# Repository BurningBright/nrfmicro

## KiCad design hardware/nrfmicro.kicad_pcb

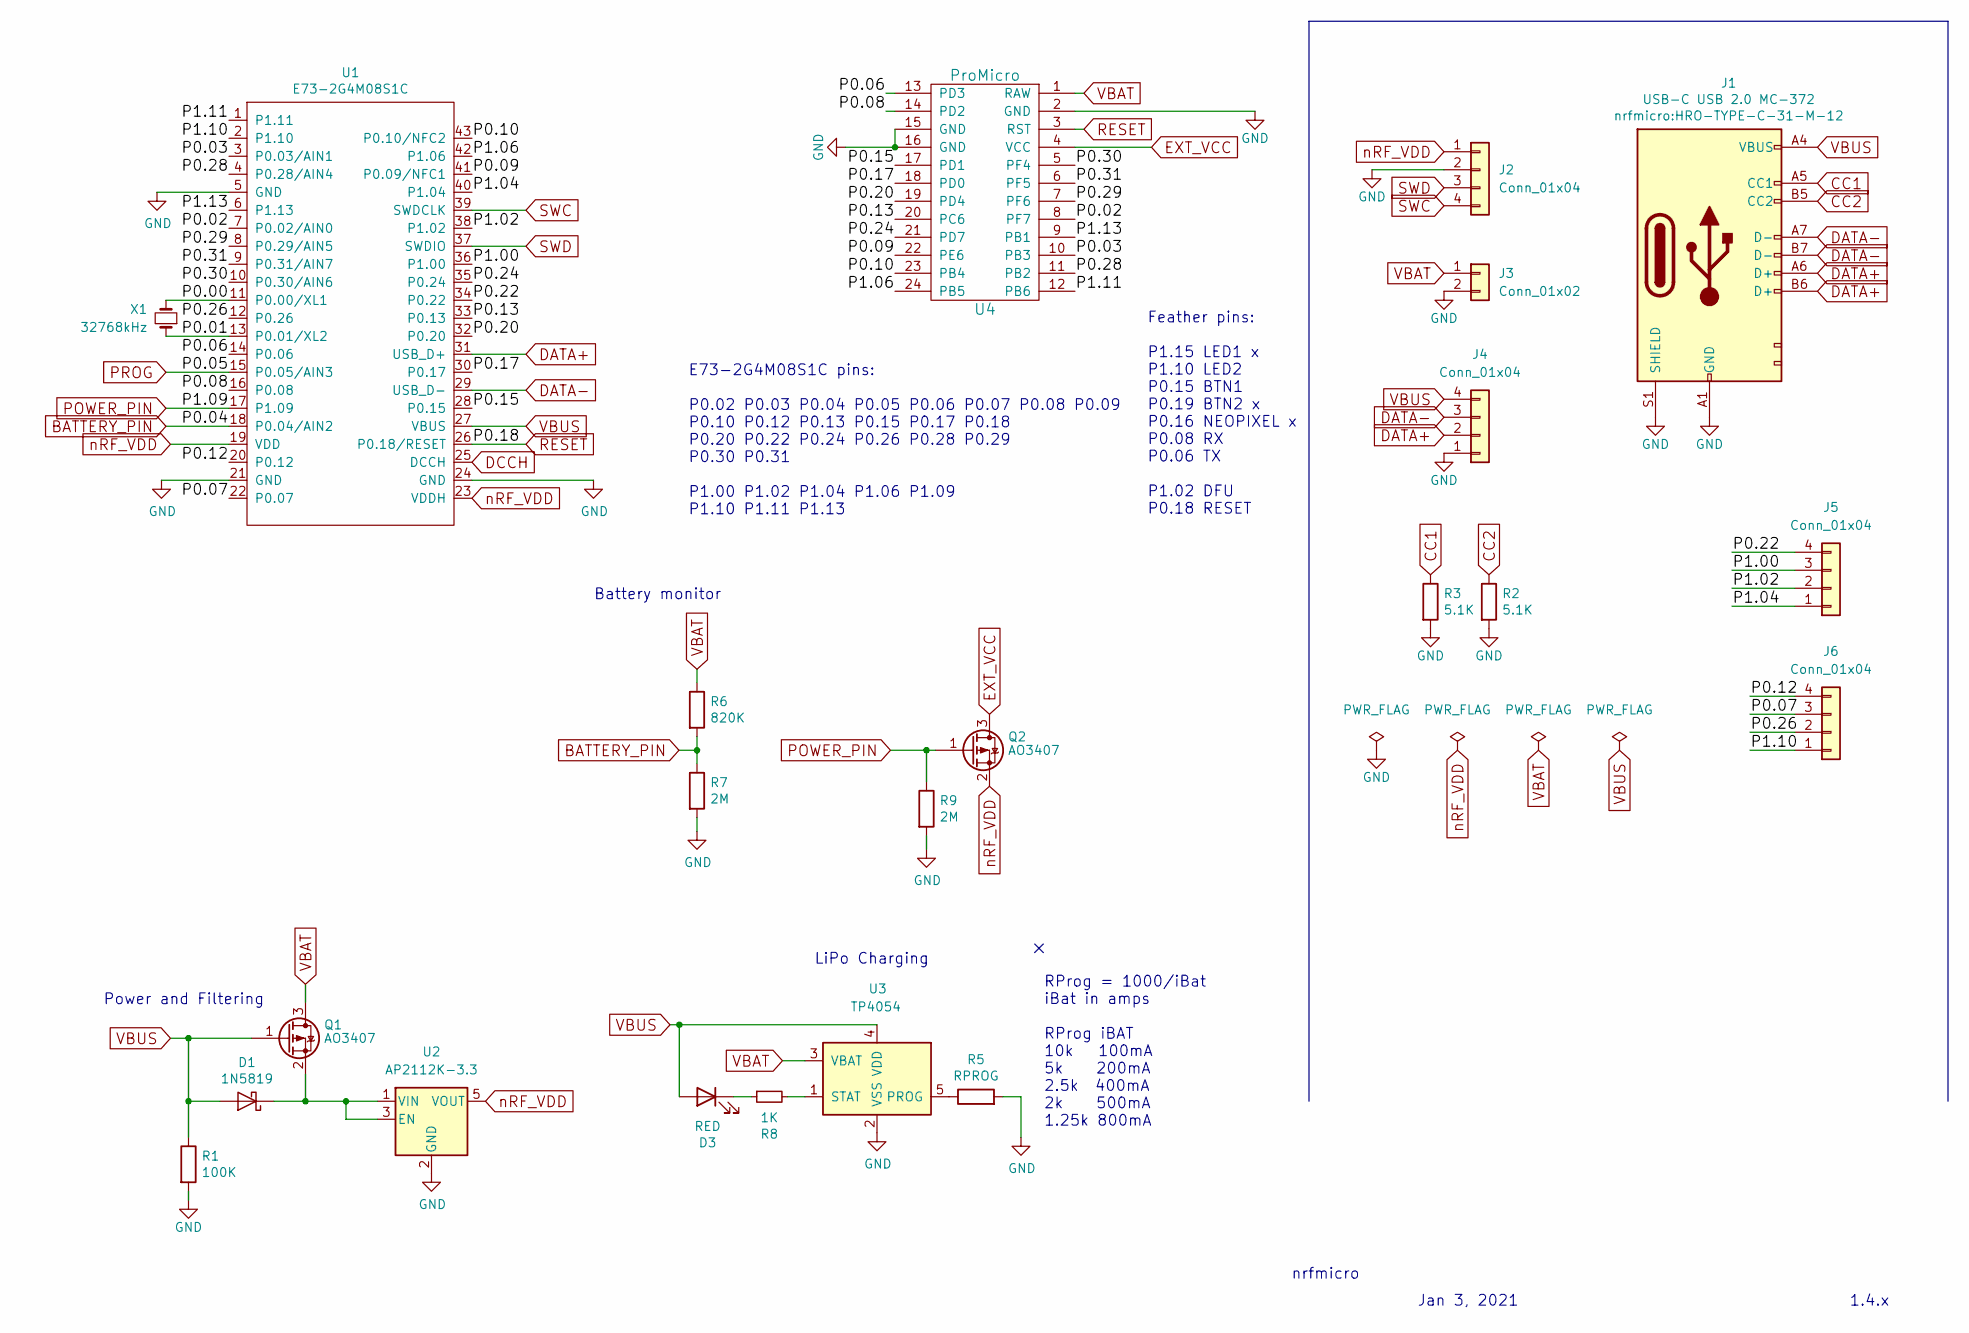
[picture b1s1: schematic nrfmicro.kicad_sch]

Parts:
D1: 1N5819; D_SOD-323F
D3: RED; LED_0603_1608Metric
J1: USB-C USB 2.0 MC-372; HRO-TYPE-C-31-M-12
J2: Conn_01x04; connector_swd
J3: Conn_01x02
J4: Conn_01x04; connector_usb
J5: Conn_01x04; connector_gpio_1
J6: Conn_01x04; connector_gpio_2
Q1, Q2: AO3407; SOT-23
R1: 100K; R_0603_1608Metric
R2, R3: 5.1K; R_0603_1608Metric
R5: RPROG; R_0603_1608Metric
R6: 820K; R_0603_1608Metric
R7, R9: 2M; R_0603_1608Metric
R8: 1K; R_0603_1608Metric
U1: E73-2G4M08S1C; E73-2G4M08S1C-52840
U2: AP2112K-3.3; SOT-23-5
U3: TP4054; SOT-23-5
U4: ProMicro; pro_micro
X1: 32768kHz

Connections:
/P0.00: U1.11 (P0.00/XL1), X1.2
/P0.01: U1.13 (P0.01/XL2), X1.1
/P0.02: U1.7 (P0.02/AIN0), U4.8 (PF7)
/P0.03: U1.3 (P0.03/AIN1), U4.10 (PB3)
/P0.06: U1.14 (P0.06), U4.13 (PD3)
/P0.07: J6.3, U1.22 (P0.07)
/P0.08: U1.16 (P0.08), U4.14 (PD2)
/P0.09: U1.41 (P0.09/NFC1), U4.22 (PE6)
/P0.10: U1.43 (P0.10/NFC2), U4.23 (PB4)
/P0.12: J6.4, U1.20 (P0.12)
/P0.13: U1.33 (P0.13), U4.20 (PC6)
/P0.15: U1.28 (P0.15), U4.17 (PD1)
/P0.17: U1.30 (P0.17), U4.18 (PD0)
/P0.20: U1.32 (P0.20), U4.19 (PD4)
/P0.22: J5.4, U1.34 (P0.22)
/P0.24: U1.35 (P0.24), U4.21 (PD7)
/P0.26: J6.2, U1.12 (P0.26)
/P0.28: U1.4 (P0.28/AIN4), U4.11 (PB2)
/P0.29: U1.8 (P0.29/AIN5), U4.7 (PF6)
/P0.30: U1.10 (P0.30/AIN6), U4.5 (PF4)
/P0.31: U1.9 (P0.31/AIN7), U4.6 (PF5)
/P1.00: J5.3, U1.36 (P1.00)
/P1.02: J5.2, U1.38 (P1.02)
/P1.04: J5.1, U1.40 (P1.04)
/P1.06: U1.42 (P1.06), U4.24 (PB5)
/P1.10: J6.1, U1.2 (P1.10)
/P1.11: U1.1 (P1.11), U4.12 (PB6)
/P1.13: U1.6 (P1.13), U4.9 (PB1)
BATTERY_PIN: R6.2, R7.1, U1.18 (P0.04/AIN2)
CC1: J1.A5 (CC1), R3.1
CC2: J1.B5 (CC2), R2.1
DATA+: J1.A6 (D+), J1.B6 (D+), J4.2, U1.31 (USB_D+)
DATA-: J1.A7 (D-), J1.B7 (D-), J4.3, U1.29 (USB_D-)
DCCH: U1.25 (DCCH)
EXT_VCC: Q2.3 (D), U4.4 (VCC)
GND: J1.A1 (GND), J1.S1 (SHIELD), J2.2, J3.2, J4.1, R1.2, R2.2, R3.2, R5.2, R7.2, R9.2, U1.5 (GND), U1.21 (GND), U1.24 (GND), U2.2 (GND), U3.2 (VSS), U4.2 (GND), U4.15 (GND), U4.16 (GND)
unnamed: D1.1 (K), Q1.2 (S), U2.1 (VIN), U2.3 (EN)
unnamed: D3.1 (K), R8.1
unnamed: R5.1, U3.5 (PROG)
unnamed: R8.2, U3.1 (STAT)
POWER_PIN: Q2.1 (G), R9.1, U1.17 (P1.09)
PROG: U1.15 (P0.05/AIN3)
RESET: U1.26 (P0.18/RESET), U4.3 (RST)
SWC: J2.4, U1.39 (SWDCLK)
SWD: J2.3, U1.37 (SWDIO)
VBAT: J3.1, Q1.3 (D), R6.1, U3.3 (VBAT), U4.1 (RAW)
VBUS: D1.2 (A), D3.2 (A), J1.A4 (VBUS), J4.4, Q1.1 (G), R1.1, U1.27 (VBUS), U3.4 (VDD)
nRF_VDD: J2.1, Q2.2 (S), U1.19 (VDD), U1.23 (VDDH), U2.5 (VOUT)

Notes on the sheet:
LiPo Charging
Jan 3, 2021
1.4.x
RProg = 1000/iBat iBat in amps RProg iBAT 10k 100mA 5k 200mA 2.5k 400mA 2k 500mA 1.25k 800mA
Power and Filtering
nrfmicro
Battery monitor
E73-2G4M08S1C pins: P0.02 P0.03 P0.04 P0.05 P0.06 P0.07 P0.08 P0.09 P0.10 P0.12 P0.13 P0.15 P0.17 P0.18 P0.20 P0.22 P0.24 P0.26 P0.28 P0.29 P0.30 P0.31 P1.00 P1.02 P1.04 P1.06 P1.09 P1.10 P1.11 P1.13
Feather pins: P1.15 LED1 x P1.10 LED2 P0.15 BTN1 P0.19 BTN2 x P0.16 NEOPIXEL x P0.08 RX P0.06 TX P1.02 DFU P0.18 RESET

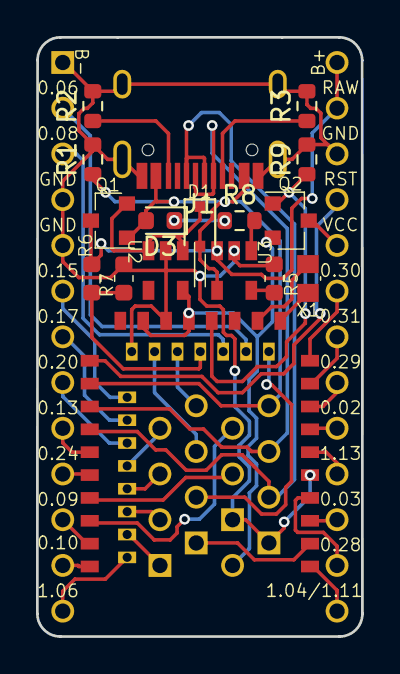
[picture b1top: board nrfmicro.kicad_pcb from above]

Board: 2 copper layers, 18.1 x 33.3 mm, 23 parts (0 on the bottom side), 46 nets.

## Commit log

2022-10-30 /** add pin */
